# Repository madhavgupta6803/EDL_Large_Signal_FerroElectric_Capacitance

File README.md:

# EDL_Large_Signal_FerroElectric_Capacitance

### Link to our Notion Page
### https://www.notion.so/EDL-MON-03-2ea75040919c4b7b8f81075fa2af05f8
#### The repository contains all the PCB schematic and routing files, the code files for the ADC, DAC, UART implementation, and the CAD files.

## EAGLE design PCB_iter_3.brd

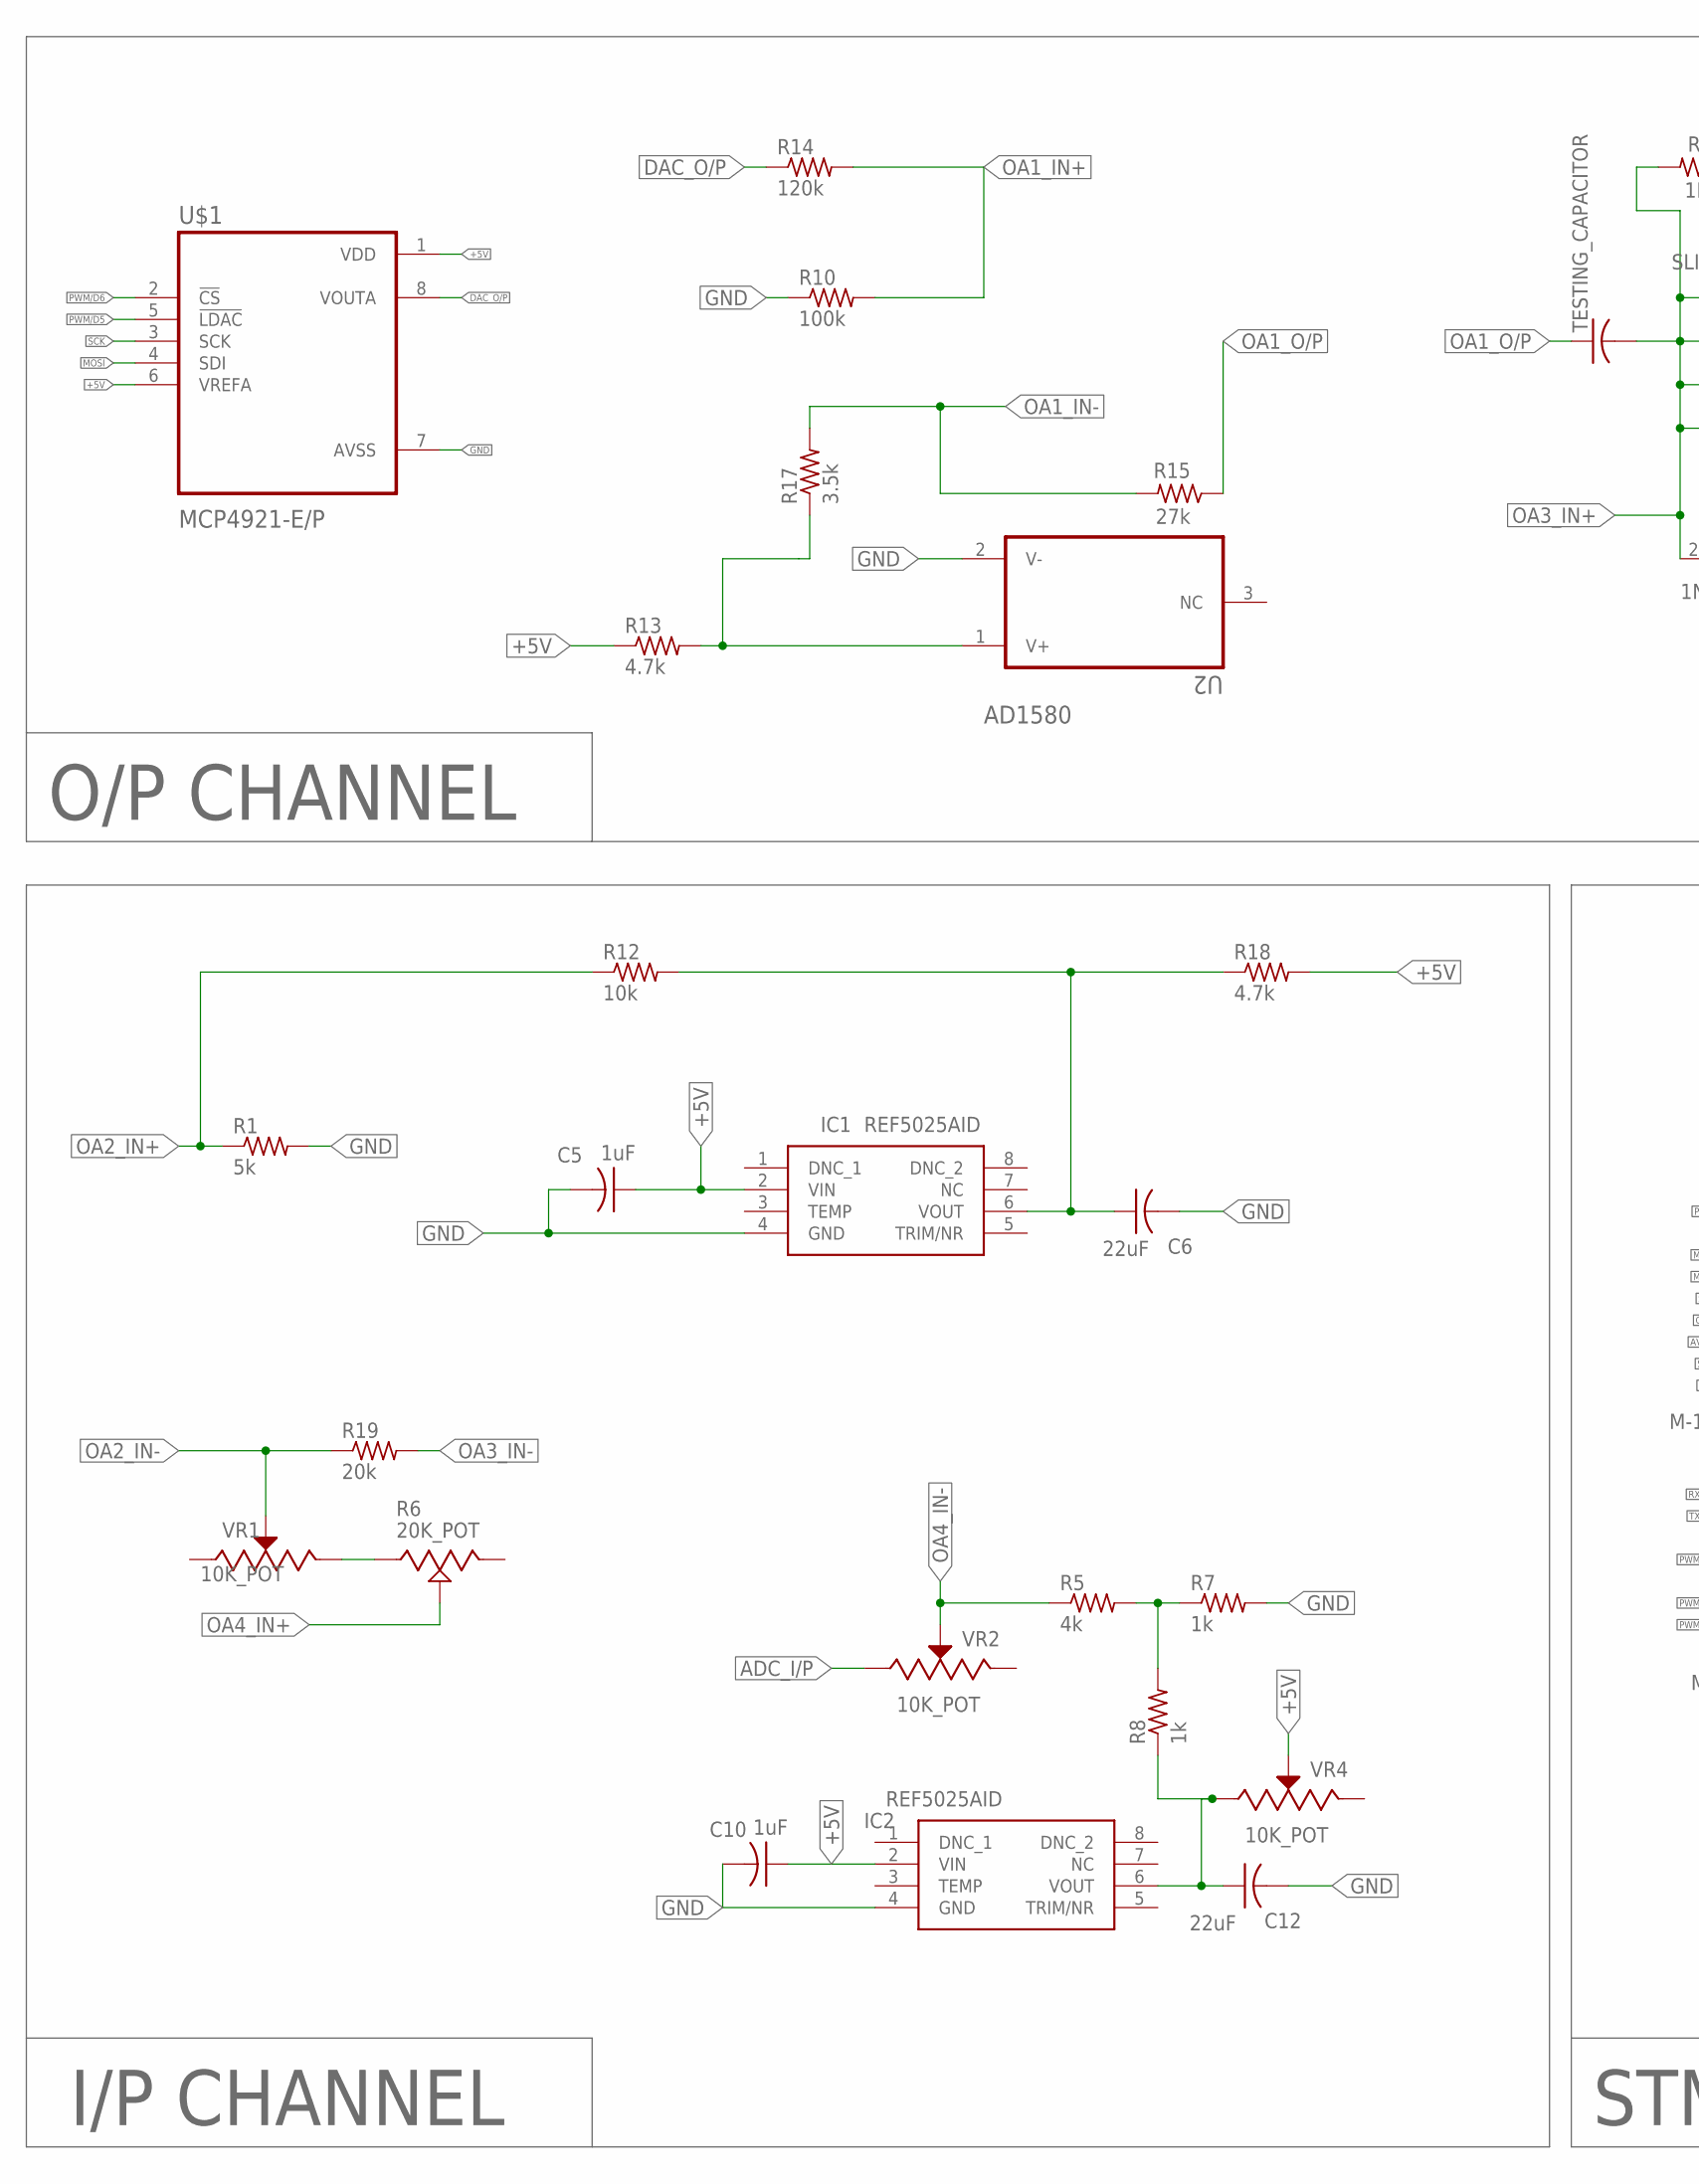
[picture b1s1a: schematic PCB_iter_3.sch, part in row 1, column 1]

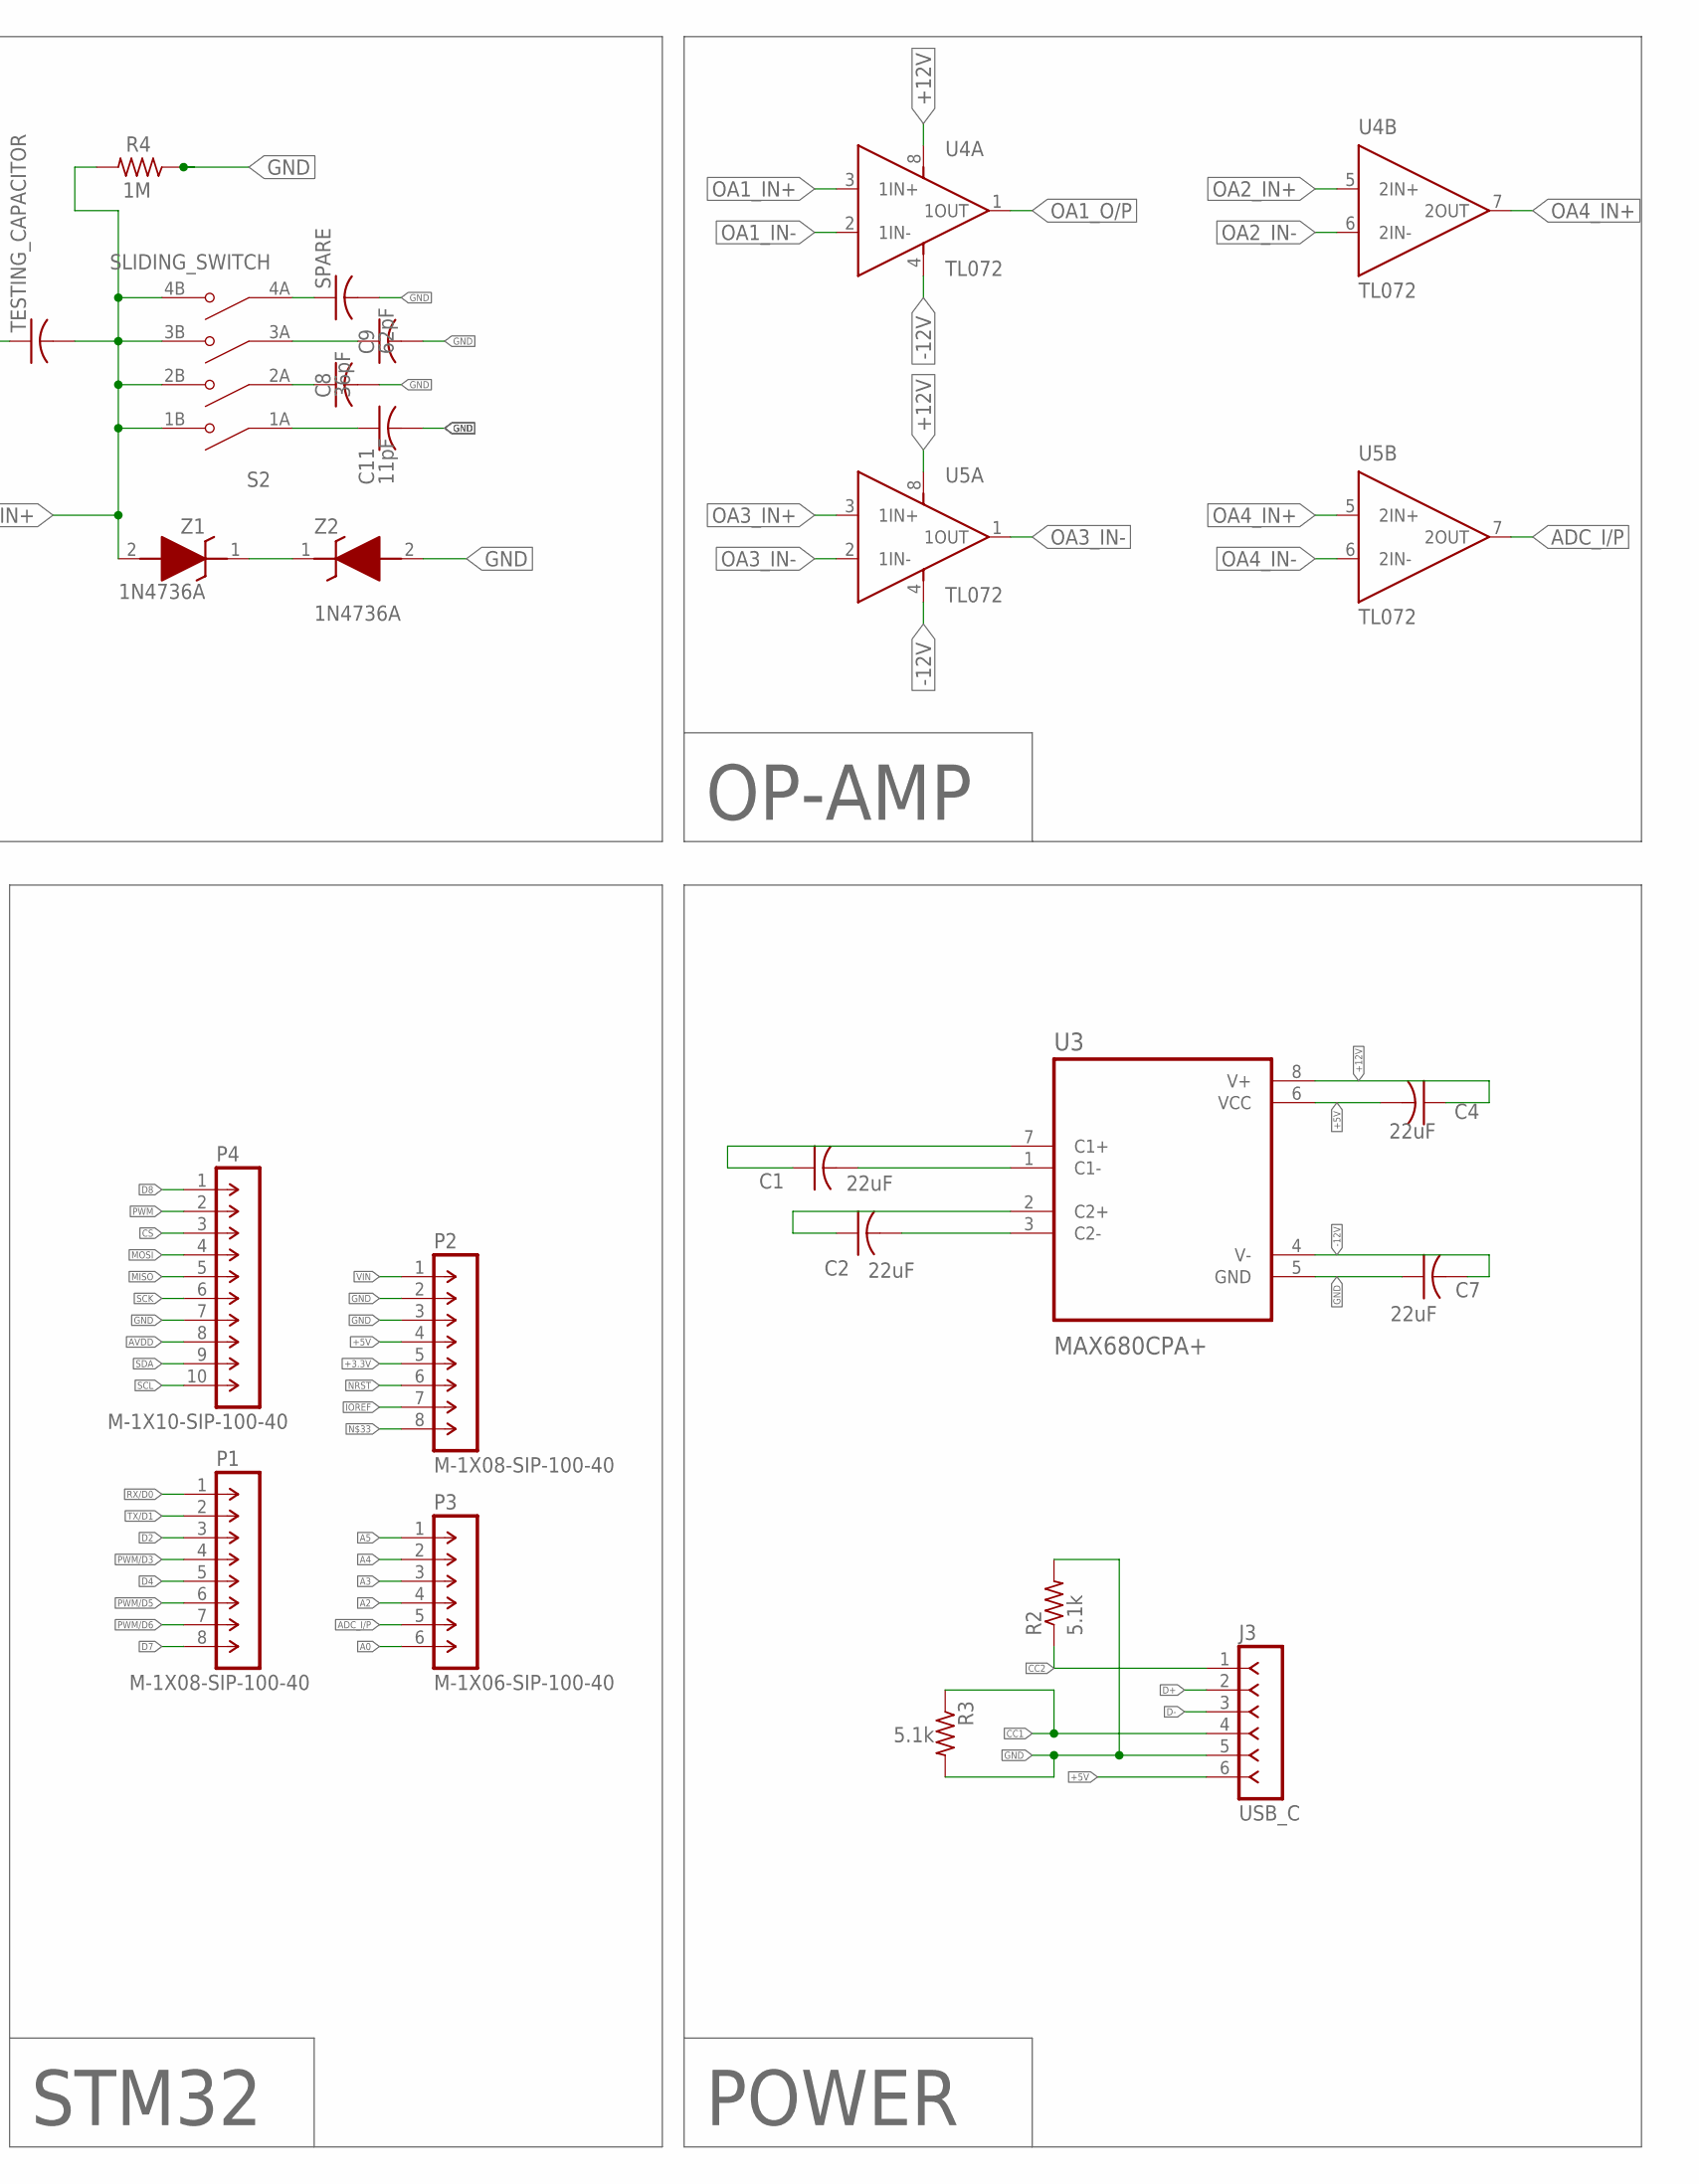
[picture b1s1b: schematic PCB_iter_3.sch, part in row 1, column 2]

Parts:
C1, C2, C4, C6, C7, C12: 22uF; C1206
C5, C10: 1uF; C1206
C8: 36pF; C1206
C9: 62pF; C1206
C11: 11pF; C1206
IC1, IC2: REF5025AID; SOIC127P600X175-8N
J3: USB_C; SIP-100-06-40Y
P1, P2: M-1X08-SIP-100-40; SIP-100-08-40
P3: M-1X06-SIP-100-40; SIP-100-06-40
P4: M-1X10-SIP-100-40; SIP-100-10-40
R1: 5k; M1206
R2, R3: 5.1k; R1206
R4: 1M; M1206
R5: 4k; M1206
R6: 20K_POT; TRIM_3296X-1-203LF
R7, R8: 1k; M1206
R10: 100k; M1206
R12: 10k; M1206
R13, R18: 4.7k; M1206
R14: 120k; M1206
R15: 27k; M1206
R17: 3.5k; M1206
R19: 20k; M1206
S2: SLIDING_SWITCH; SW_DS01C-254-S-04BE
SPARE: C-USC1206; C1206
TESTING_CAPACITOR: C-US050-030X075; C050-030X075
U2: AD1580; SOT96P237X112-3N
U3: MAX680CPA+; DIP794W47P254L991H457Q8
U4, U5: TL072; DIP794W45P254L1060H508Q8
U$1: MCP4921-E/P; DIP787W46P254L927H533Q8
VR1, VR2, VR4: 10K_POT; TRIM_3296W-1-103RLF
Z1, Z2: 1N4736A; DIOAD1413W86L463D238

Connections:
+3.3V: P2.5
+5V: C4.2, C5.1, C10.1, IC1.2 (VIN), IC2.2 (VIN), J3.6, P2.4, R13.1, R18.2, U3.6 (VCC), U$1.1 (VDD), U$1.6 (VREFA), VR4.2 (WIPER)
+12V: C4.1, U3.8 (V+), U4.8 (VCC+), U5.8 (VCC+)
-12V: C7.2, U3.4 (V-), U4.4 (VCC-), U5.4 (VCC-)
A0: P3.6
A2: P3.4
A3: P3.3
A4: P3.2
A5: P3.1
ADC_I/P: P3.5, U5.7 (2OUT), VR2.1 (CCW)
AVDD: P4.8
CC1: J3.4, R3.1
CC2: J3.1, R2.1
CS: P4.3
D2: P1.3
D4: P1.5
D7: P1.8
D8: P4.1
D+: J3.2
D-: J3.3
DAC_O/P: R14.1, U$1.8 (VOUTA)
GND: C5.2, C6.2, C7.1, C8.2, C9.2, C10.2, C11.2, C12.2, IC1.4 (GND), IC2.4 (GND), J3.5, P2.2, P2.3, P4.7, R1.2, R2.2, R3.2, R4.1, R7.2, R10.1, SPARE.2, U2.2 (V-), U3.5 (GND), U$1.7 (AVSS), Z2.2 (A)
IOREF: P2.7
MISO: P4.5
MOSI: P4.4, U$1.4 (SDI)
unnamed: R6.1 (CCW), VR1.3 (CW)
unnamed: R5.2, R7.1, R8.2
unnamed: C12.1, IC2.6 (VOUT), R8.1, VR4.1 (CCW)
unnamed: C1.2, U3.1 (C1-)
unnamed: R13.2, R17.1, U2.1 (V+)
unnamed: C6.1, IC1.6 (VOUT), R12.2, R18.1
unnamed: Z1.1 (K), Z2.1 (K)
unnamed: C1.1, U3.7 (C1+)
unnamed: C2.2, U3.3 (C2-)
unnamed: C2.1, U3.2 (C2+)
unnamed: C9.1, S2.3A (COM3)
unnamed: S2.4A (COM4), SPARE.1
unnamed: C11.1, S2.1A (COM1)
unnamed: C8.1, S2.2A (COM2)
NRST: P2.6
OA1_IN+: R10.2, R14.2, U4.3 (1IN+)
OA1_IN-: R15.2, R17.2, U4.2 (1IN-)
OA1_O/P: R15.1, TESTING_CAPACITOR.1, U4.1 (1OUT)
OA2_IN+: R1.1, R12.1, U4.5 (2IN+)
OA2_IN-: R19.1, U4.6 (2IN-), VR1.2 (WIPER)
OA3_IN+: R4.2, S2.1B (NO1), S2.2B (NO2), S2.3B (NO3), S2.4B (NO4), TESTING_CAPACITOR.2, U5.3 (1IN+), Z1.2 (A)
OA3_IN-: R19.2, U5.1 (1OUT), U5.2 (1IN-)
OA4_IN+: R6.2 (WIPER), U4.7 (2OUT), U5.5 (2IN+)
OA4_IN-: R5.1, U5.6 (2IN-), VR2.2 (WIPER)
PWM: P4.2
PWM/D3: P1.4
PWM/D5: P1.6, U$1.5 (!LDAC)
PWM/D6: P1.7, U$1.2 (!CS)
RX/D0: P1.1
SCK: P4.6, U$1.3 (SCK)
SCL: P4.10
SDA: P4.9
TX/D1: P1.2
VIN: P2.1

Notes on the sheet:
POWER
STM32
I/P CHANNEL
OP-AMP
O/P CHANNEL

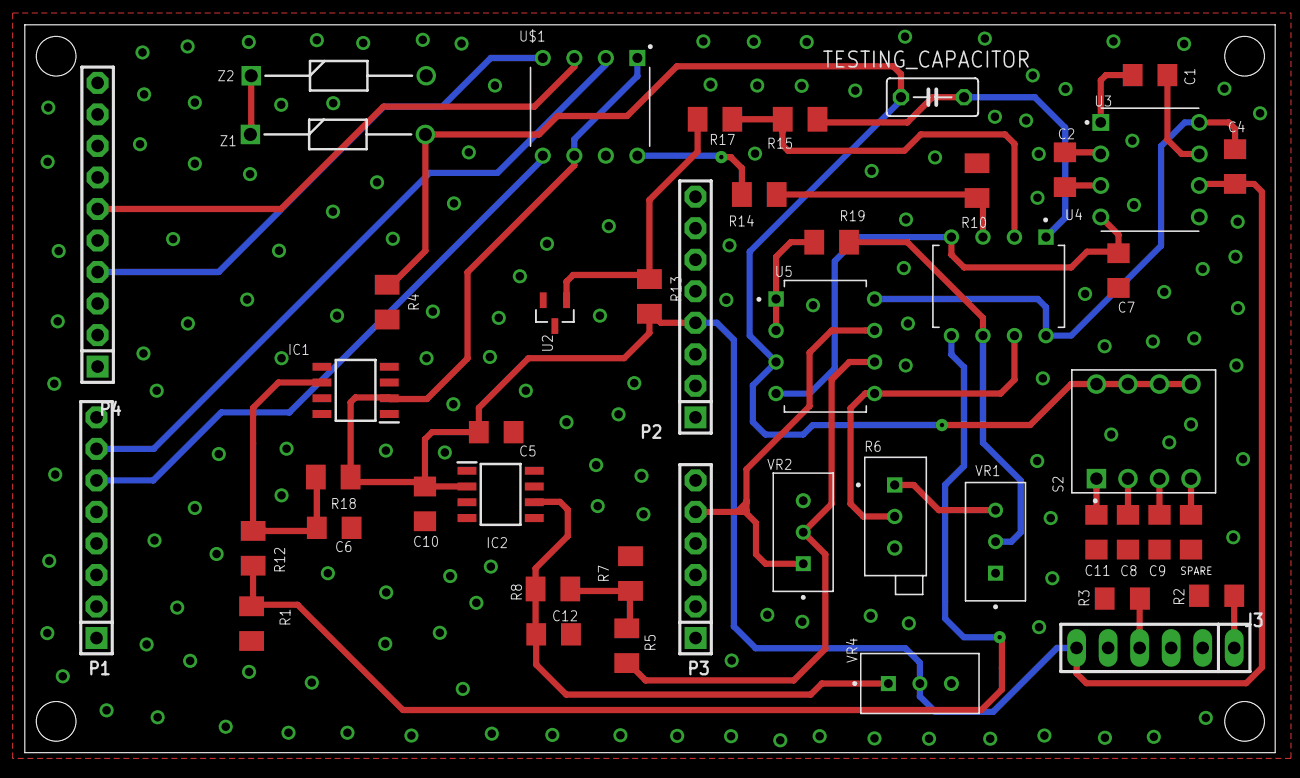
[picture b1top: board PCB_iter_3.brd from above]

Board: 2 copper layers, 100.7 x 58.6 mm, 47 parts (0 on the bottom side), 35 nets.

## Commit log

2024-03-16 Integrated Testing Results Added
2024-03-17 Added MileStone 2 PPT
2024-03-17 Added MileStone 1 PPT
2024-03-17 DAC Testing Video Added
2024-03-17 Added PCB Files
2024-03-17 Added CAD File
2024-03-18 Add files via upload
    Added a non-inverting amplifier with dc offset
2024-03-19 Updated Simulation
    Currently does not give the right o/p. Changed diode in the upper circuit. Giving 2.5V using a diode. Changed the resistor values of the new op-amp as well.
2024-03-24 PCB ITERATION 2
2024-03-24 Uploaded the BOM
2024-03-27 PCB ITERATION 3
    Added holes on 4 corners with updated placement and routing
2024-03-29 PCB ITERATION 4
2024-04-02 STM_ADC_DAC_Code Added
2024-04-02 FPGA DAC Files Added
2024-04-15 Added the GUI code file

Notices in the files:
parts and their libraries:
con-headers-jp: Copyright (C) 2008, Bob Starr
